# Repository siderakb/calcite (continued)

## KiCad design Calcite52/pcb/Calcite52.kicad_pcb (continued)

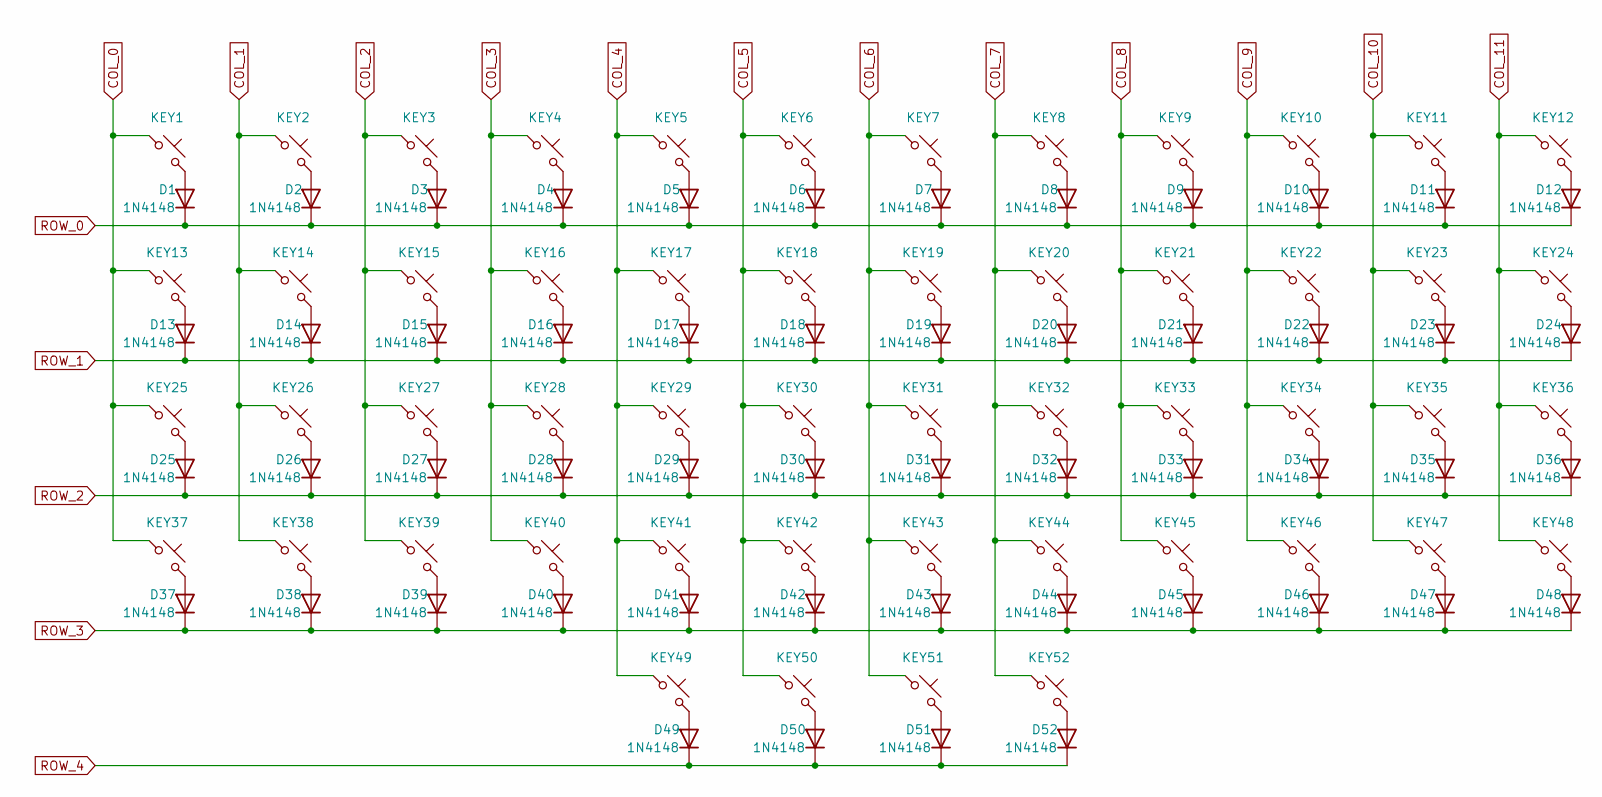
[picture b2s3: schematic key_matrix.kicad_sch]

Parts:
D1, D2, D3, D4, D5, D6, D7, D8, D9, D10, D11, D12, D13, D14, D15, D16, D17, D18, D19, D20, D21, D22, D23, D24, D25, D26, D27, D28, D29, D30, D31, D32, D33, D34, D35, D36, D37, D38, D39, D40, D41, D42, D43, D44, D45, D46, D47, D48, D49, D50, D51, D52: 1N4148; D_SOD-123; MFR. Part # 1N4148W; LCSC C81598
KEY1, KEY2, KEY3, KEY4, KEY5, KEY6, KEY7, KEY8, KEY9, KEY10, KEY11, KEY12, KEY13, KEY14, KEY15, KEY16, KEY17, KEY18, KEY19, KEY20, KEY21, KEY22, KEY23, KEY24, KEY25, KEY26, KEY27, KEY28, KEY29, KEY30, KEY31, KEY32, KEY33, KEY34, KEY35, KEY36, KEY37, KEY38, KEY39, KEY40, KEY41, KEY42, KEY43, KEY44, KEY45, KEY46, KEY47, KEY48, KEY49, KEY50, KEY51, KEY52: SW_Push_45deg; Kailh_Choc_PG1350_THT_A

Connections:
COL_0: KEY1.1, KEY13.1, KEY25.1, KEY37.1; also elsewhere on the board
COL_1: KEY2.1, KEY14.1, KEY26.1, KEY38.1; also elsewhere on the board
COL_2: KEY3.1, KEY15.1, KEY27.1, KEY39.1; also elsewhere on the board
COL_3: KEY4.1, KEY16.1, KEY28.1, KEY40.1; also elsewhere on the board
COL_4: KEY5.1, KEY17.1, KEY29.1, KEY41.1, KEY49.1; also elsewhere on the board
COL_5: KEY6.1, KEY18.1, KEY30.1, KEY42.1, KEY50.1; also elsewhere on the board
COL_6: KEY7.1, KEY19.1, KEY31.1, KEY43.1, KEY51.1; also elsewhere on the board
COL_7: KEY8.1, KEY20.1, KEY32.1, KEY44.1, KEY52.1; also elsewhere on the board
COL_8: KEY9.1, KEY21.1, KEY33.1, KEY45.1; also elsewhere on the board
COL_9: KEY10.1, KEY22.1, KEY34.1, KEY46.1; also elsewhere on the board
COL_10: KEY11.1, KEY23.1, KEY35.1, KEY47.1; also elsewhere on the board
COL_11: KEY12.1, KEY24.1, KEY36.1, KEY48.1; also elsewhere on the board
unnamed: D1.2 (A), KEY1.2
unnamed: D2.2 (A), KEY2.2
unnamed: D3.2 (A), KEY3.2
unnamed: D4.2 (A), KEY4.2
unnamed: D5.2 (A), KEY5.2
unnamed: D6.2 (A), KEY6.2
unnamed: D7.2 (A), KEY7.2
unnamed: D8.2 (A), KEY8.2
unnamed: D9.2 (A), KEY9.2
unnamed: D10.2 (A), KEY10.2
unnamed: D11.2 (A), KEY11.2
unnamed: D12.2 (A), KEY12.2
unnamed: D13.2 (A), KEY13.2
unnamed: D14.2 (A), KEY14.2
unnamed: D15.2 (A), KEY15.2
unnamed: D16.2 (A), KEY16.2
unnamed: D17.2 (A), KEY17.2
unnamed: D18.2 (A), KEY18.2
unnamed: D19.2 (A), KEY19.2
unnamed: D20.2 (A), KEY20.2
unnamed: D21.2 (A), KEY21.2
unnamed: D22.2 (A), KEY22.2
unnamed: D23.2 (A), KEY23.2
unnamed: D24.2 (A), KEY24.2
unnamed: D25.2 (A), KEY25.2
unnamed: D26.2 (A), KEY26.2
unnamed: D27.2 (A), KEY27.2
unnamed: D28.2 (A), KEY28.2
unnamed: D29.2 (A), KEY29.2
unnamed: D30.2 (A), KEY30.2
unnamed: D31.2 (A), KEY31.2
unnamed: D32.2 (A), KEY32.2
unnamed: D33.2 (A), KEY33.2
unnamed: D34.2 (A), KEY34.2
unnamed: D35.2 (A), KEY35.2
unnamed: D36.2 (A), KEY36.2
unnamed: D37.2 (A), KEY37.2
unnamed: D38.2 (A), KEY38.2
unnamed: D39.2 (A), KEY39.2
unnamed: D40.2 (A), KEY40.2
unnamed: D41.2 (A), KEY41.2
unnamed: D42.2 (A), KEY42.2
unnamed: D43.2 (A), KEY43.2
unnamed: D44.2 (A), KEY44.2
unnamed: D45.2 (A), KEY45.2
unnamed: D46.2 (A), KEY46.2
unnamed: D47.2 (A), KEY47.2
unnamed: D48.2 (A), KEY48.2
unnamed: D49.2 (A), KEY49.2
unnamed: D50.2 (A), KEY50.2
unnamed: D51.2 (A), KEY51.2
unnamed: D52.2 (A), KEY52.2
ROW_0: D1.1 (K), D2.1 (K), D3.1 (K), D4.1 (K), D5.1 (K), D6.1 (K), D7.1 (K), D8.1 (K), D9.1 (K), D10.1 (K), D11.1 (K), D12.1 (K); also elsewhere on the board
ROW_1: D13.1 (K), D14.1 (K), D15.1 (K), D16.1 (K), D17.1 (K), D18.1 (K), D19.1 (K), D20.1 (K), D21.1 (K), D22.1 (K), D23.1 (K), D24.1 (K); also elsewhere on the board
ROW_2: D25.1 (K), D26.1 (K), D27.1 (K), D28.1 (K), D29.1 (K), D30.1 (K), D31.1 (K), D32.1 (K), D33.1 (K), D34.1 (K), D35.1 (K), D36.1 (K); also elsewhere on the board
ROW_3: D37.1 (K), D38.1 (K), D39.1 (K), D40.1 (K), D41.1 (K), D42.1 (K), D43.1 (K), D44.1 (K), D45.1 (K), D46.1 (K), D47.1 (K), D48.1 (K); also elsewhere on the board
ROW_4: D49.1 (K), D50.1 (K), D51.1 (K), D52.1 (K); also elsewhere on the board

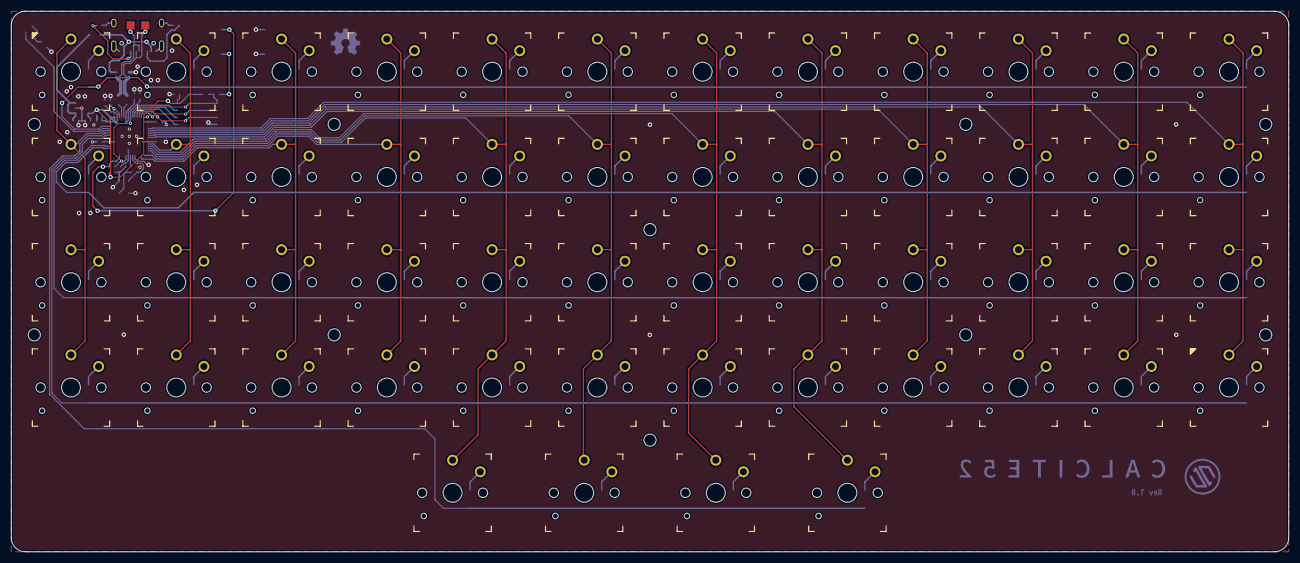
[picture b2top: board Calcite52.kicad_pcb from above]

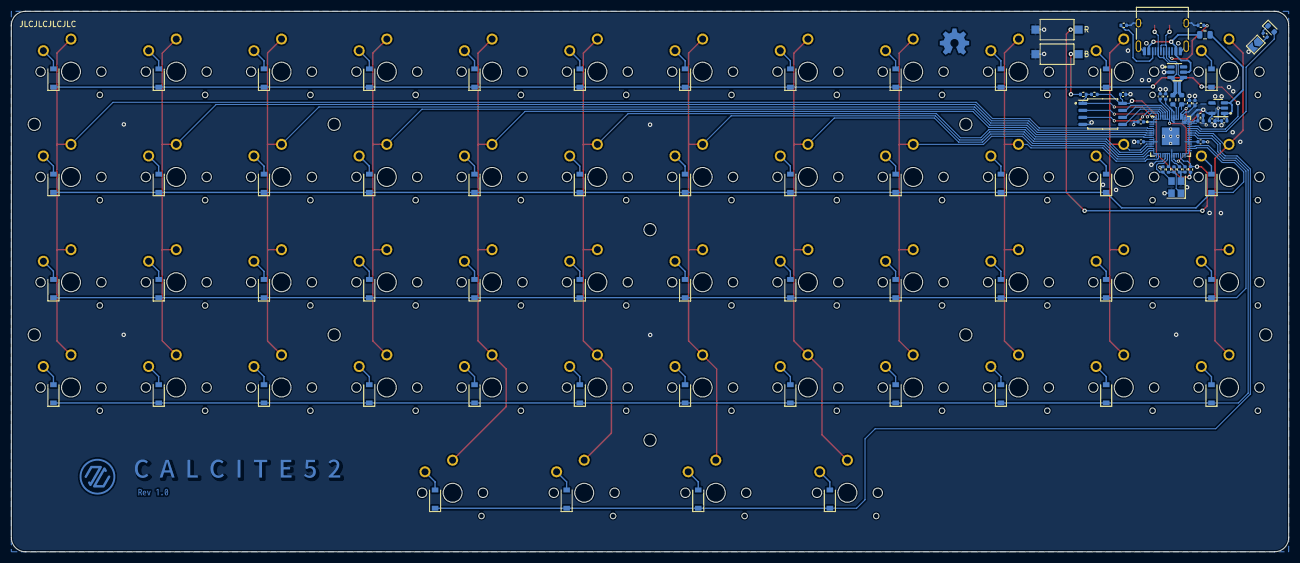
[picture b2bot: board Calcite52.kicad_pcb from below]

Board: 2 copper layers, 231.1 x 97.8 mm, 153 parts (89 on the bottom side), 94 nets.

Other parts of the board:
kibuzzard-63E64B4D: G***; kibuzzard-63E64B4D

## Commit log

2023-02-05 Add .gitignore
2023-02-05 Add KiCad project
2023-02-05 Add submodule-key-switches.putty
2023-02-05 Update submodule
2023-02-08 Update PCB layout, basically finished
2023-02-09 full routed
2023-02-09 Rename, from Fula52 to Calcite52
2023-02-09 Rename
2023-02-09 Update layout
2023-02-10 Update layout and logo
2023-02-10 Create LICENSE
2023-03-03 Update BOM
2023-03-08 Add PCB center mark at "User.4" layer
2023-03-08 Add case FreeCAD 3D model
2023-03-15 Add case 30 model
2023-03-15 Update project
2023-03-15 Update .gitinore for FreeCAD
2023-03-16 Update case
2023-04-29 Add keyboard-layout-editor JSON file
2023-04-29 Add project footprint library table
2023-04-29 Update KiCad files from `v6.0.8` to `v7.0.2`
2023-04-29 Update README.md
    Fix typo
2023-06-25 Update URL, replace "ziteh" with "siderakb".
2023-06-29 Update Vial-QMK url
2023-07-06 Move Calcite52 files
2023-07-06 Created Calcite60
2023-07-06 Add Calcite60 readme
2023-07-06 Remove .log
2023-07-06 Update footprint libraries path
2023-07-07 Reduce the size of the USB protrusion
2023-07-07 Update board size
2023-07-07 Add KiCanvas url
2023-07-08 Add calcite60 case
2023-07-08 Update image
2023-11-01 Update Calcite60 Rev2
2024-01-06 Update board setup
2024-01-06 Routed
2024-01-14 Update LICENSE
2024-01-26 Add Calcite52 case
2024-04-17 Update switch footprint from TS-1064S to TS1064SA
2025-04-17 chore: add `.gitattributes`
2025-04-26 Add PCBA Calaite60
2025-05-01 feat: add rev1 back
2025-05-01 feat: update footprint lib
2025-05-02 feat: add rev3
2025-11-06 chore: update submodule
